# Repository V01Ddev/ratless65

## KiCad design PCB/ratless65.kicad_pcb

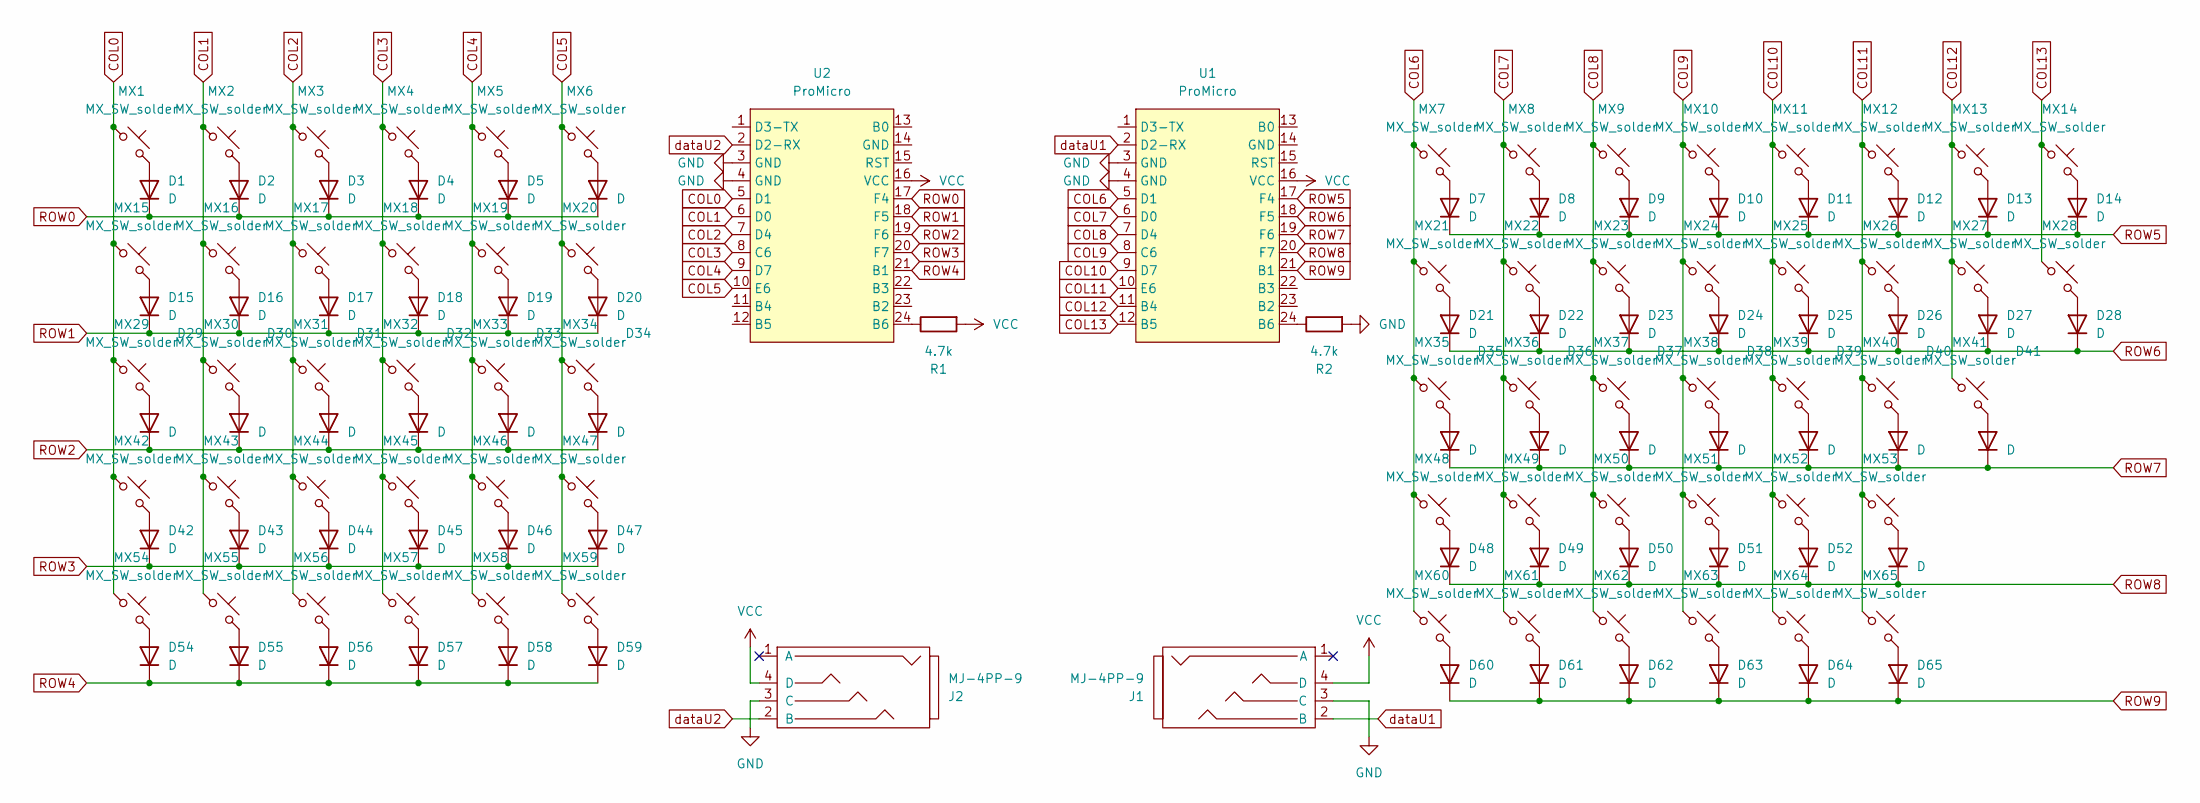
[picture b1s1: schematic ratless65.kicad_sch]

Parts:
D1, D2, D3, D4, D5, D6, D7, D8, D9, D10, D11, D12, D13, D14, D15, D16, D17, D18, D19, D20, D21, D22, D23, D24, D25, D26, D27, D28, D29, D30, D31, D32, D33, D34, D35, D36, D37, D38, D39, D40, D41, D42, D43, D44, D45, D46, D47, D48, D49, D50, D51, D52, D53, D54, D55, D56, D57, D58, D59, D60, D61, D62, D63, D64, D65: D; D_SOD-123
J1, J2: MJ-4PP-9
MX1, MX15, MX29, MX41, MX42, MX53, MX59, MX60: MX_SW_solder; SW_MX_1.5u
MX2, MX3, MX4, MX5, MX6, MX7, MX8, MX9, MX10, MX11, MX12, MX13, MX16, MX17, MX18, MX19, MX20, MX21, MX22, MX23, MX24, MX25, MX26, MX27, MX30, MX31, MX32, MX33, MX34, MX35, MX36, MX37, MX38, MX39, MX40, MX43, MX44, MX45, MX46, MX47, MX48, MX49, MX50, MX51, MX52, MX54, MX55, MX56, MX57, MX58, MX61, MX62, MX63, MX64, MX65: MX_SW_solder; SW_MX_1u
MX14, MX28: MX_SW_solder; SW_MX_1.25u
R1, R2: 4.7k; R_1206_3216Metric
U1, U2: ProMicro; ProMicro_USBup

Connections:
COL0: MX1.1, MX15.1, MX29.1, MX42.1, MX54.1, U2.5 (D1)
COL1: MX2.1, MX16.1, MX30.1, MX43.1, MX55.1, U2.6 (D0)
COL2: MX3.1, MX17.1, MX31.1, MX44.1, MX56.1, U2.7 (D4)
COL3: MX4.1, MX18.1, MX32.1, MX45.1, MX57.1, U2.8 (C6)
COL4: MX5.1, MX19.1, MX33.1, MX46.1, MX58.1, U2.9 (D7)
COL5: MX6.1, MX20.1, MX34.1, MX47.1, MX59.1, U2.10 (E6)
COL6: MX7.1, MX21.1, MX35.1, MX48.1, MX60.1, U1.5 (D1)
COL7: MX8.1, MX22.1, MX36.1, MX49.1, MX61.1, U1.6 (D0)
COL8: MX9.1, MX23.1, MX37.1, MX50.1, MX62.1, U1.7 (D4)
COL9: MX10.1, MX24.1, MX38.1, MX51.1, MX63.1, U1.8 (C6)
COL10: MX11.1, MX25.1, MX39.1, MX52.1, MX64.1, U1.9 (D7)
COL11: MX12.1, MX26.1, MX40.1, MX53.1, MX65.1, U1.10 (E6)
COL12: MX13.1, MX27.1, MX41.1, U1.11 (B4)
COL13: MX14.1, MX28.1, U1.12 (B5)
GND: J1.3 (C), J2.3 (C), R2.2, U1.3 (GND), U1.4 (GND), U2.3 (GND), U2.4 (GND)
unnamed: D1.2 (A), MX1.2
unnamed: D2.2 (A), MX2.2
unnamed: D3.2 (A), MX3.2
unnamed: D4.2 (A), MX4.2
unnamed: D5.2 (A), MX5.2
unnamed: D6.2 (A), MX6.2
unnamed: D7.2 (A), MX7.2
unnamed: D8.2 (A), MX8.2
unnamed: D9.2 (A), MX9.2
unnamed: D10.2 (A), MX10.2
unnamed: D11.2 (A), MX11.2
unnamed: D12.2 (A), MX12.2
unnamed: D13.2 (A), MX13.2
unnamed: D14.2 (A), MX14.2
unnamed: D15.2 (A), MX15.2
unnamed: D16.2 (A), MX16.2
unnamed: D17.2 (A), MX17.2
unnamed: D18.2 (A), MX18.2
unnamed: D19.2 (A), MX19.2
unnamed: D20.2 (A), MX20.2
unnamed: D21.2 (A), MX21.2
unnamed: D22.2 (A), MX22.2
unnamed: D23.2 (A), MX23.2
unnamed: D24.2 (A), MX24.2
unnamed: D25.2 (A), MX25.2
unnamed: D26.2 (A), MX26.2
unnamed: D27.2 (A), MX27.2
unnamed: D28.2 (A), MX28.2
unnamed: D29.2 (A), MX29.2
unnamed: D30.2 (A), MX30.2
unnamed: D31.2 (A), MX31.2
unnamed: D32.2 (A), MX32.2
unnamed: D33.2 (A), MX33.2
unnamed: D34.2 (A), MX34.2
unnamed: D35.2 (A), MX35.2
unnamed: D36.2 (A), MX36.2
unnamed: D37.2 (A), MX37.2
unnamed: D38.2 (A), MX38.2
unnamed: D39.2 (A), MX39.2
unnamed: D40.2 (A), MX40.2
unnamed: D41.2 (A), MX41.2
unnamed: D42.2 (A), MX42.2
unnamed: D43.2 (A), MX43.2
unnamed: D44.2 (A), MX44.2
unnamed: D45.2 (A), MX45.2
unnamed: D46.2 (A), MX46.2
unnamed: D47.2 (A), MX47.2
unnamed: D48.2 (A), MX48.2
unnamed: D49.2 (A), MX49.2
unnamed: D50.2 (A), MX50.2
unnamed: D51.2 (A), MX51.2
unnamed: D52.2 (A), MX52.2
unnamed: D53.2 (A), MX53.2
unnamed: D54.2 (A), MX54.2
unnamed: D55.2 (A), MX55.2
unnamed: D56.2 (A), MX56.2
unnamed: D57.2 (A), MX57.2
unnamed: D58.2 (A), MX58.2
unnamed: D59.2 (A), MX59.2
unnamed: D60.2 (A), MX60.2
unnamed: D61.2 (A), MX61.2
unnamed: D62.2 (A), MX62.2
unnamed: D63.2 (A), MX63.2
unnamed: D64.2 (A), MX64.2
unnamed: D65.2 (A), MX65.2
unnamed: R2.1, U1.24 (B6)
unnamed: R1.1, U2.24 (B6)
ROW0: D1.1 (K), D2.1 (K), D3.1 (K), D4.1 (K), D5.1 (K), D6.1 (K), U2.17 (F4)
ROW1: D15.1 (K), D16.1 (K), D17.1 (K), D18.1 (K), D19.1 (K), D20.1 (K), U2.18 (F5)
ROW2: D29.1 (K), D30.1 (K), D31.1 (K), D32.1 (K), D33.1 (K), D34.1 (K), U2.19 (F6)
ROW3: D42.1 (K), D43.1 (K), D44.1 (K), D45.1 (K), D46.1 (K), D47.1 (K), U2.20 (F7)
ROW4: D54.1 (K), D55.1 (K), D56.1 (K), D57.1 (K), D58.1 (K), D59.1 (K), U2.21 (B1)
ROW5: D7.1 (K), D8.1 (K), D9.1 (K), D10.1 (K), D11.1 (K), D12.1 (K), D13.1 (K), D14.1 (K), U1.17 (F4)
ROW6: D21.1 (K), D22.1 (K), D23.1 (K), D24.1 (K), D25.1 (K), D26.1 (K), D27.1 (K), D28.1 (K), U1.18 (F5)
ROW7: D35.1 (K), D36.1 (K), D37.1 (K), D38.1 (K), D39.1 (K), D40.1 (K), D41.1 (K), U1.19 (F6)
ROW8: D48.1 (K), D49.1 (K), D50.1 (K), D51.1 (K), D52.1 (K), D53.1 (K), U1.20 (F7)
ROW9: D60.1 (K), D61.1 (K), D62.1 (K), D63.1 (K), D64.1 (K), D65.1 (K), U1.21 (B1)
VCC: J1.4 (D), J2.4 (D), R1.2, U1.16 (VCC), U2.16 (VCC)
dataU1: J1.2 (B), U1.2 (D2-RX)
dataU2: J2.2 (B), U2.2 (D2-RX)

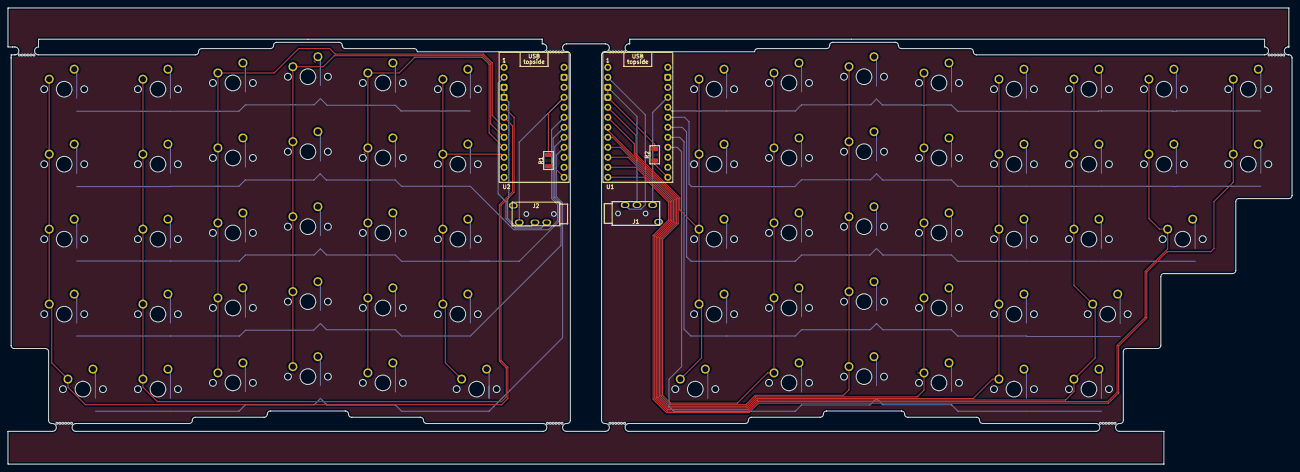
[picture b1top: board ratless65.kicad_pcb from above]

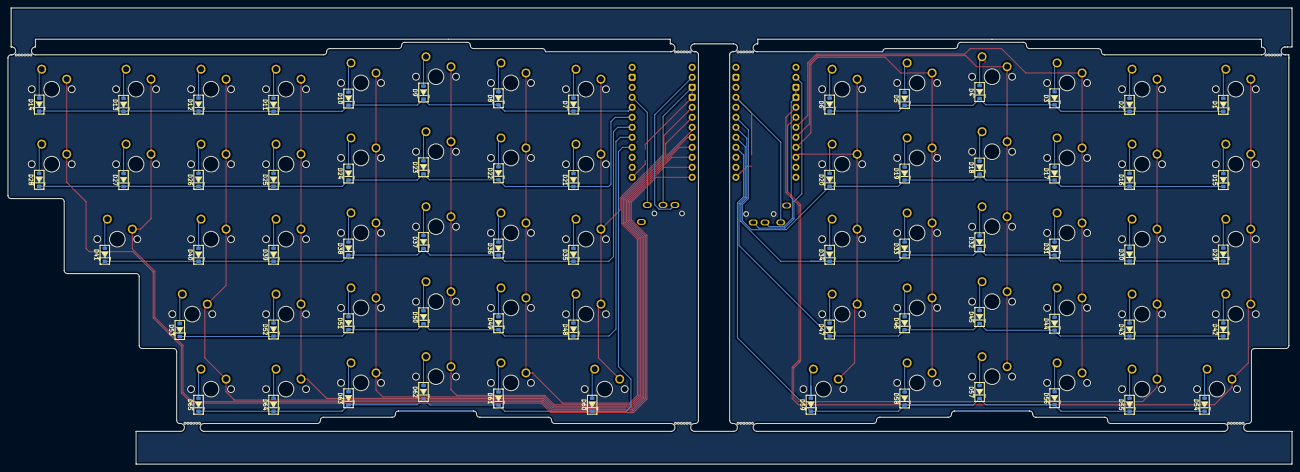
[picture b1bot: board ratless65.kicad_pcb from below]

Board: 2 copper layers, 326.2 x 115.9 mm, 136 parts (65 on the bottom side), 95 nets.

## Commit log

2024-05-04 Finished switch matrix, yet to layout switches on the pcb
2024-05-04 Removed unneeded .gitignore
2024-05-04 Moved Kicad .gitignore to PCB directory
2024-05-05 Started wiring to the MCUs + Added TRRS jacks + Lots...
2024-05-11 Finished PCB, need to add resistors for I2C
2024-06-10 I have no clue what changed but just want everything synced
